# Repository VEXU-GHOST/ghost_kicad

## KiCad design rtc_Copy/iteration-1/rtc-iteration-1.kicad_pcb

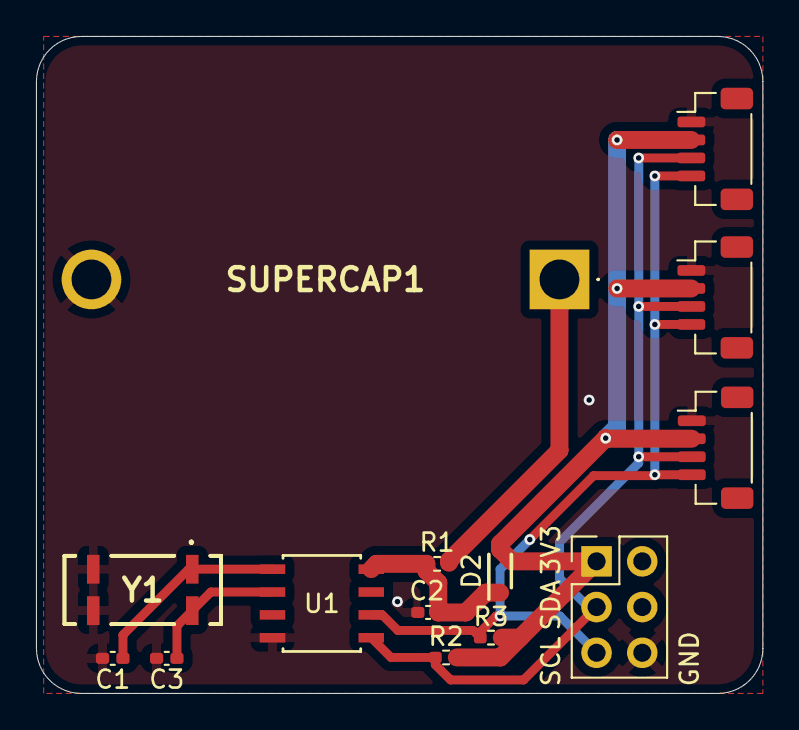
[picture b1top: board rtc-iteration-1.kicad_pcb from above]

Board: 2 copper layers, 40.4 x 36.5 mm, 14 parts (0 on the bottom side), 8 nets.

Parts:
C1, C3: 24p; C_0402_1005Metric_Pad0.74x0.62mm_HandSolder
C2: 0.1u; C_0402_1005Metric_Pad0.74x0.62mm_HandSolder
D2: RB751V-40X_R1; SODFL2512X90N
J1: Conn_02x03_Odd_Even; PinHeader_2x03_P2.54mm_Vertical
J2, J3, J4: Conn_01x04; JST_SH_BM04B-SRSS-TB_1x04-1MP_P1.00mm_Vertical
R1: 20k; R_0402_1005Metric_Pad0.72x0.64mm_HandSolder
R2, R3: 2.5k; R_0402_1005Metric_Pad0.72x0.64mm_HandSolder
SUPERCAP1: 5; CE5R5505HFZJ
U1: PCF8563T/5_518; PCF8563T_5_518_U_SO8_NXP
Y1: LFXTAL016178REEL

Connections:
+3.3V: D2.2 (A), J1.1, J2.2, J3.2, J4.2, R2.2, R3.2
GND: C1.2, C2.2, C3.2, J1.6, J2.1, J3.1, J4.1, SUPERCAP1.2 (-), U1.4 (VSS), Y1.2 (N/C_1), Y1.3 (N/C_2)
unnamed: C2.1, D2.1 (K), R1.2, U1.8 (VDD)
unnamed: R1.1, SUPERCAP1.1 (+)
unnamed: C1.1, U1.1 (OSCI), Y1.1 (CRYSTAL_1)
unnamed: C3.1, U1.2 (OSCO), Y1.4 (CRYSTAL_2)
scl: J1.5, J2.4, J3.4, J4.4, R3.1, U1.6 (SCL)
sda: J1.3, J2.3, J3.3, J4.3, R2.1, U1.5 (SDA)

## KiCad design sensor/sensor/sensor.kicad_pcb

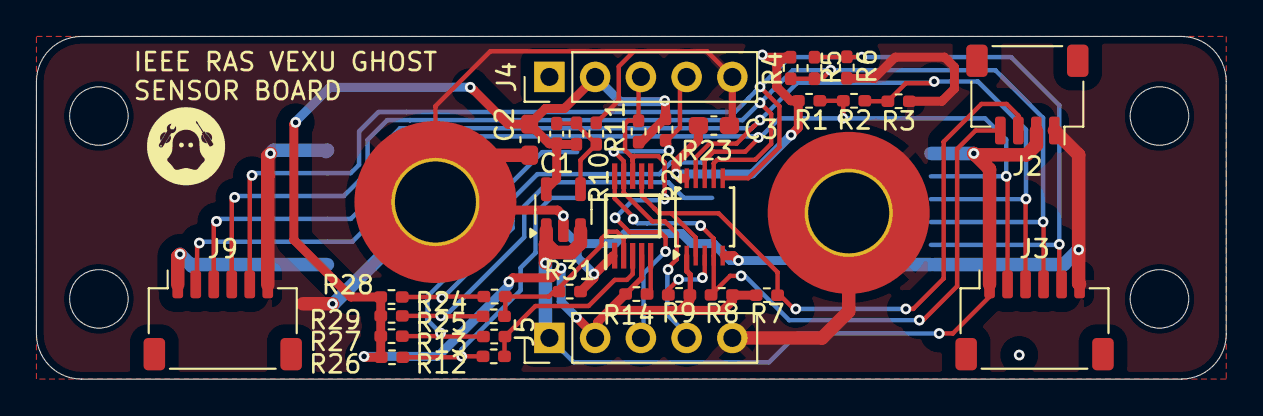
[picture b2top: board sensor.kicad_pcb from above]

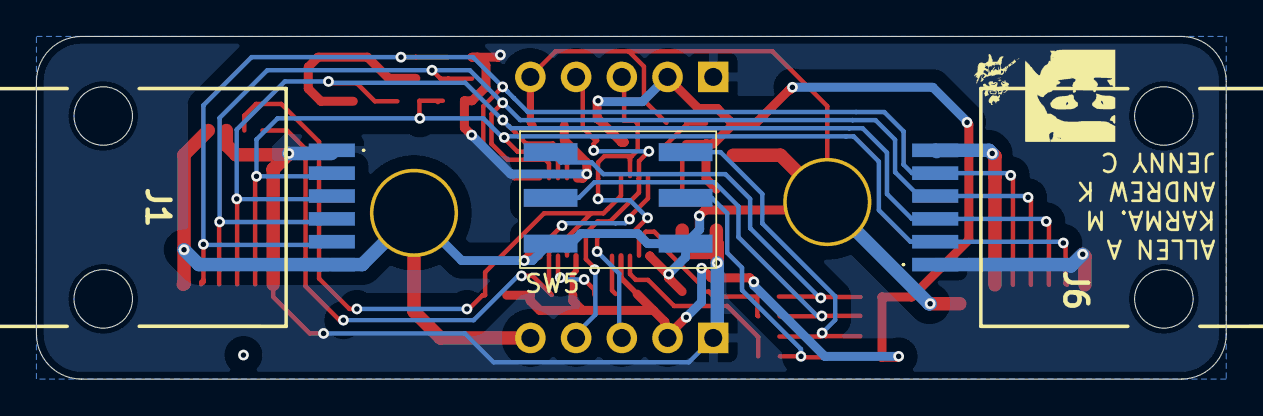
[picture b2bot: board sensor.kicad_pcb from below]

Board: 2 copper layers, 66.1 x 19.0 mm, 39 parts (3 on the bottom side), 20 nets.

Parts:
C1: 1n; C_0402_1005Metric_Pad0.74x0.62mm_HandSolder
C2, C3: 1u; C_0603_1608Metric_Pad1.08x0.95mm_HandSolder
H1, H2: MountingHole_Pad; MountingHole_4.5mm_Pad_TopOnly
IC1: LTC4316CMS#TRPBF; SOP50P490X110-10N
J1, J6: GDLX-SMT-N-66; GDLXSMTN66
J2: Conn_01x04; JST_SH_SM04B-SRSS-TB_1x04-1MP_P1.00mm_Horizontal
J3, J9: Conn_01x06; JST_SH_SM06B-SRSS-TB_1x06-1MP_P1.00mm_Horizontal
J4, J5: Conn_01x05; PinHeader_1x05_P2.54mm_Vertical
R1, R3, R4, R6: 600; R_0402_1005Metric_Pad0.72x0.64mm_HandSolder
R2, R5: 120; R_0402_1005Metric_Pad0.72x0.64mm_HandSolder
R7, R8, R22, R23: 4.7k; R_0402_1005Metric_Pad0.72x0.64mm_HandSolder
R9, R14, R26, R27: 10k; R_0402_1005Metric_Pad0.72x0.64mm_HandSolder
R10: 52k; R_0402_1005Metric_Pad0.72x0.64mm_HandSolder
R11: 30k; R_0402_1005Metric_Pad0.72x0.64mm_HandSolder
R12, R24: 400k; R_0402_1005Metric_Pad0.72x0.64mm_HandSolder
R13: 750k; R_0402_1005Metric_Pad0.72x0.64mm_HandSolder
R25: 780k; R_0402_1005Metric_Pad0.72x0.64mm_HandSolder
R28: 80k; R_0402_1005Metric_Pad0.72x0.64mm_HandSolder
R29: 40k; R_0402_1005Metric_Pad0.72x0.64mm_HandSolder
R31: 260k; R_0402_1005Metric_Pad0.72x0.64mm_HandSolder
SW5: SW_Coded_SH-7050; Rotary_Switch_16_pos
U1: PCA9615DP; TSSOP-10_3x3mm_P0.5mm
U5: TPS73101DBV; SOT-23-5

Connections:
+3.3V: C1.1, C2.1, IC1.4 (VCC), J4.2, J5.2, R7.1, R8.1, R9.1, R10.1, R14.2, R22.1, R23.1, R26.1, R27.1, R28.1, R29.1, U1.1 (V_{DD(A)}), U5.5 (OUT)
+5V: C3.1, J1.1, J2.2, J3.1, J4.1, J5.1, J6.1, J9.1, R1.1, R4.1, U1.10 (V_{DD(B)}), U5.1 (IN), U5.3 (EN)
/Sensors/scl: IC1.9 (SCLOUT), J4.4, J5.4, R23.2
/Sensors/sda: IC1.8 (SDAOUT), J4.3, J5.3, R22.2
GND: C2.2, C3.2, H1.1, H2.1, IC1.1 (GND), J1.6, J2.1, J3.6, J4.5, J5.5, J6.6, J9.6, R3.2, R6.2, R11.2, R31.2, SW5.C, U1.5 (V_{SS}), U5.2 (GND)
unnamed: IC1.5 (ENABLE), R14.1
unnamed: IC1.10 (SCLIN), J2.4, R8.2, U1.4 (SCL)
unnamed: IC1.7 (SDAIN), J2.3, R7.2, U1.2 (SDA)
unnamed: IC1.2 (XORH), R24.2, R25.2, R31.1
unnamed: IC1.3 (XORL), R12.2, R13.2
unnamed: J1.2, J3.2, J6.2, J9.2, R1.2, R2.2, U1.8 (DSDAP)
unnamed: J1.3, J3.3, J6.3, J9.3, R2.1, R3.1, U1.9 (DSDAM)
unnamed: J1.4, J3.4, J6.4, J9.4, R4.2, R5.2, U1.7 (DSCLP)
unnamed: J1.5, J3.5, J6.5, J9.5, R5.1, R6.1, U1.6 (DSCLM)
unnamed: R12.1, R26.2, SW5.1
unnamed: R13.1, R27.2, SW5.2
unnamed: R24.1, R28.2, SW5.4
unnamed: R25.1, R29.2, SW5.8
unnamed: R9.2, U1.3 (EN)
unnamed: C1.2, R10.2, R11.1, U5.4 (FB)

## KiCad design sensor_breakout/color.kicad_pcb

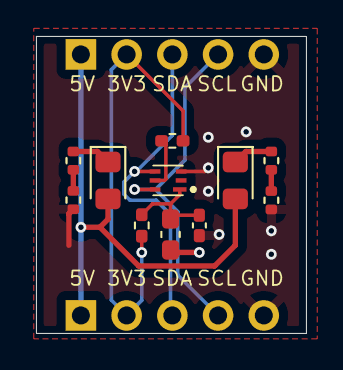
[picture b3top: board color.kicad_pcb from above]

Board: 2 copper layers, 15.0 x 16.5 mm, 13 parts (0 on the bottom side), 11 nets.

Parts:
C4: 1u; C_0603_1608Metric_Pad1.08x0.95mm_HandSolder
C5: 0.1u; C_0402_1005Metric_Pad0.74x0.62mm_HandSolder
D1, D2: WHITE; LED_0805_2012Metric_Pad1.15x1.40mm_HandSolder
IC2: ISL29125IROZ-T7; ISL29125IROZT7
J4, J4#2: Conn_01x05; PinHeader_1x05_P2.54mm_Vertical
R15: 100; R_0402_1005Metric_Pad0.72x0.64mm_HandSolder
R16: 4.7k; R_0402_1005Metric_Pad0.72x0.64mm_HandSolder
R17, R18, R30, R32: 120; R_0402_1005Metric

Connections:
+3.3V: J4.2, J4#2.2, R15.2, R16.1
+5V: D1.2 (A), D2.2 (A), J4.1, J4#2.1
/scl: IC2.6 (SCL), J4.4, J4#2.4
/sda: IC2.4 (SDA), J4.3, J4#2.3
GND: C4.2, C5.2, IC2.3 (GND), J4.5, J4#2.5, R30.2, R32.2
unnamed: D1.1 (K), R17.1
unnamed: D2.1 (K), R18.1
unnamed: C4.1, C5.1, IC2.1 (VDD), R15.1
unnamed: IC2.5 (~INT), R16.2
unnamed: R17.2, R30.1
unnamed: R18.2, R32.1

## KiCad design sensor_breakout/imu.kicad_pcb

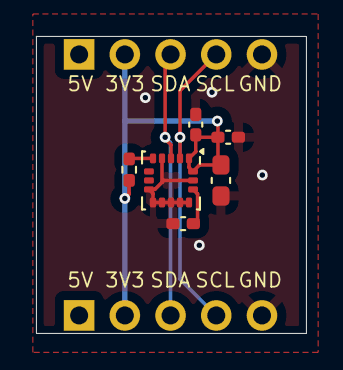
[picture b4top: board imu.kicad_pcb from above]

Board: 2 copper layers, 15.0 x 16.5 mm, 8 parts (0 on the bottom side), 7 nets.

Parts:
C7, C10: 0.1u; C_0402_1005Metric_Pad0.74x0.62mm_HandSolder
C8: 2.2u; C_0603_1608Metric_Pad1.08x0.95mm_HandSolder
C9: 10n; C_0402_1005Metric_Pad0.74x0.62mm_HandSolder
J4, J4#2: Conn_01x05; PinHeader_1x05_P2.54mm_Vertical
R19: 4.7k; R_0402_1005Metric_Pad0.72x0.64mm_HandSolder
U6: ICM-20602; LGA-16_3x3mm_P0.5mm_LayoutBorder3x5y

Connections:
+3.3V: C7.1, C8.1, C9.1, J4.2, J4#2.2, R19.1, U6.1 (VDDIO), U6.16 (VDD)
+5V: J4.1, J4#2.1
/scl: J4.4, J4#2.4, U6.2 (SCL/SPC)
/sda: J4.3, J4#2.3, U6.3 (SDA/SDI)
GND: C7.2, C8.2, C9.2, C10.2, J4.5, J4#2.5, U6.4 (SAO/SD0), U6.8 (FSYNC), U6.9 (GND), U6.10 (GND), U6.11 (GND), U6.12 (GND), U6.13 (GND), U6.15 (GND)
unnamed: C10.1, U6.14 (REGOUT)
unnamed: R19.2, U6.5 (~CS)

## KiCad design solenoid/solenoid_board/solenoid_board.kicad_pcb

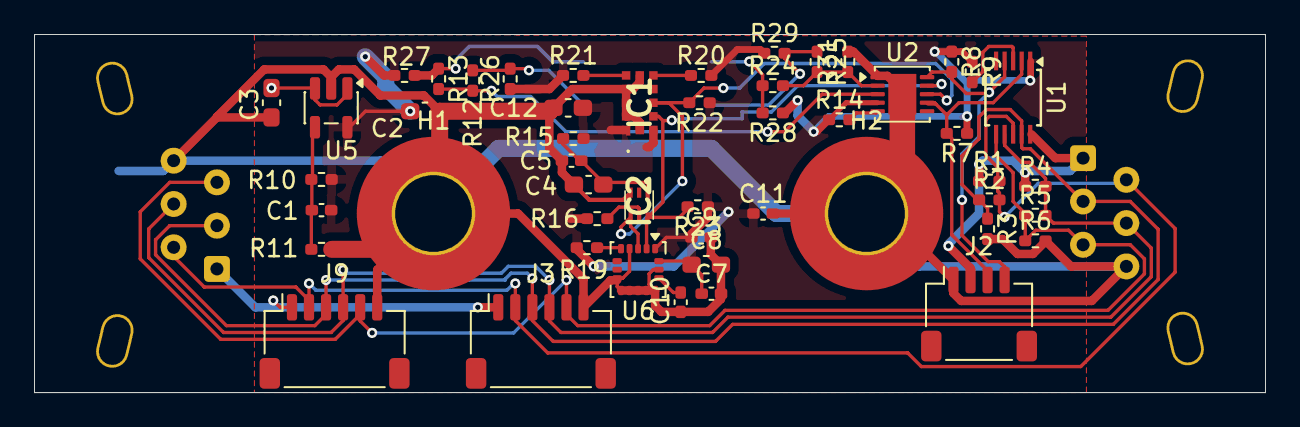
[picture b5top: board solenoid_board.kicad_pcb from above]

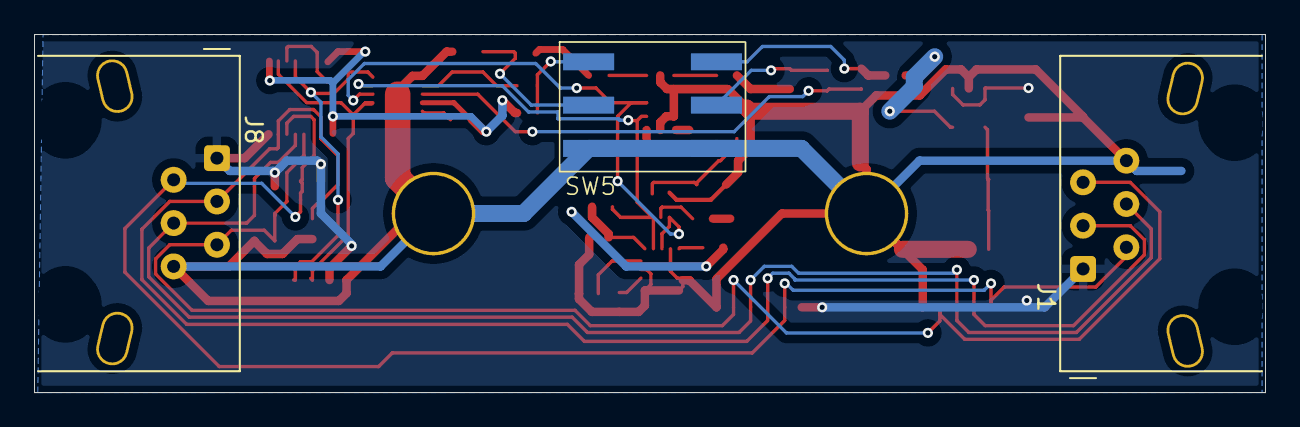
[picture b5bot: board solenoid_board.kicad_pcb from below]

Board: 4 copper layers, 72.2 x 21.0 mm, 53 parts (3 on the bottom side), 26 nets.

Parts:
C1: 1n; C_0402_1005Metric_Pad0.74x0.62mm_HandSolder
C2, C3, C4: 1u; C_0603_1608Metric_Pad1.08x0.95mm_HandSolder
C5, C7, C10, C11: 0.1u; C_0402_1005Metric_Pad0.74x0.62mm_HandSolder
C8: 2.2u; C_0603_1608Metric_Pad1.08x0.95mm_HandSolder
C9: 10n; C_0402_1005Metric_Pad0.74x0.62mm_HandSolder
C12: 4.7u; C_0603_1608Metric_Pad1.08x0.95mm_HandSolder
H1, H2: MountingHole_Pad; MountingHole_4.5mm_Pad_TopOnly
IC1: VL53L4CDV0DH_1; VL53L4CDV0DH1
IC2: ISL29125IROZ-T7; ISL29125IROZT7
J1, J8: RJ12_Shielded; RJ12_Pin_Connector
J2: Conn_01x04; JST_SH_SM04B-SRSS-TB_1x04-1MP_P1.00mm_Horizontal
J3, J9: Conn_01x06; JST_SH_SM06B-SRSS-TB_1x06-1MP_P1.00mm_Horizontal
R1, R3, R4, R6: 600; R_0402_1005Metric_Pad0.72x0.64mm_HandSolder
R2, R5: 120; R_0402_1005Metric_Pad0.72x0.64mm_HandSolder
R7, R8, R16, R19, R22, R23: 4.7k; R_0402_1005Metric_Pad0.72x0.64mm_HandSolder
R9, R14, R20, R21, R26, R27: 10k; R_0402_1005Metric_Pad0.72x0.64mm_HandSolder
R10: 52k; R_0402_1005Metric_Pad0.72x0.64mm_HandSolder
R11: 30k; R_0402_1005Metric_Pad0.72x0.64mm_HandSolder
R12, R24: 400k; R_0402_1005Metric_Pad0.72x0.64mm_HandSolder
R13: 750k; R_0402_1005Metric_Pad0.72x0.64mm_HandSolder
R15: 100; R_0402_1005Metric_Pad0.72x0.64mm_HandSolder
R25: 780k; R_0402_1005Metric_Pad0.72x0.64mm_HandSolder
R28: 80k; R_0402_1005Metric_Pad0.72x0.64mm_HandSolder
R29: 40k; R_0402_1005Metric_Pad0.72x0.64mm_HandSolder
R31: 260k; R_0402_1005Metric_Pad0.72x0.64mm_HandSolder
SW5: SW_Coded_SH-7050; Rotary_Switch_16_pos
U1: PCA9615DP; TSSOP-10_3x3mm_P0.5mm
U2: LTC4316xDD; DFN-10-1EP_3x3mm_P0.5mm_EP1.65x2.38mm
U5: TPS73101DBV; SOT-23-5
U6: ICM-20602; LGA-16_3x3mm_P0.5mm_LayoutBorder3x5y

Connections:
+3.3V: C1.1, C2.1, C7.1, C8.1, C9.1, C11.1, C12.1, IC1.1 (AVDDVCSEL_1), IC1.11 (AVDD), IC1.13 (AVDDVCSEL_2), R7.1, R8.1, R9.1, R10.1, R14.1, R15.2, R16.1, R19.1, R20.2, R21.1, R22.1, R23.1, R26.1, R27.1, R28.1, R29.1, U1.1 (V_{DD(A)}), U2.4 (V_{CC}), U5.5 (OUT), U6.1 (VDDIO), U6.16 (VDD)
+5V: C3.1, J1.1, J2.2, J3.1, J8.1, J9.1, R1.1, R4.1, U1.10 (V_{DD(B)}), U5.1 (IN), U5.3 (EN)
/Sensors/scl: IC1.10 (SCL), IC2.6 (SCL), R23.2, U2.9 (SCLOUT), U6.2 (SCL/SPC)
/Sensors/sda: IC1.9 (SDA), IC2.4 (SDA), R22.2, U2.8 (SDAOUT), U6.3 (SDA/SDI)
GND: C2.2, C3.2, C4.2, C5.2, C7.2, C8.2, C9.2, C10.2, C11.2, C12.2, H1.1, H2.1, IC1.2 (AVSSVCSEL), IC1.3 (GND), IC1.4 (GND2), IC1.6 (GND3), IC1.12 (GND4), IC2.3 (GND), J1.6, J2.1, J3.6, J8.6, J9.6, R3.2, R6.2, R11.2, R31.2, SW5.C, U1.5 (V_{SS}), U2.1 (GND), U2.11 (EP), U5.2 (GND), U6.4 (SAO/SD0), U6.8 (FSYNC), U6.9 (GND), U6.10 (GND), U6.11 (GND), U6.12 (GND), U6.13 (GND), U6.15 (GND)
unnamed: IC1.7 (GPIO1), R20.1
unnamed: IC1.5 (XSHUT), R21.2
unnamed: C4.1, C5.1, IC2.1 (VDD), R15.1
unnamed: IC2.5 (~INT), R16.2
unnamed: J2.3, R7.2, U1.2 (SDA), U2.7 (SDAIN)
unnamed: J2.4, R8.2, U1.4 (SCL), U2.10 (SCLIN)
unnamed: J1.2, J3.2, J8.2, J9.2, R1.2, R2.2, U1.8 (DSDAP)
unnamed: J1.3, J3.3, J8.3, J9.3, R2.1, R3.1, U1.9 (DSDAM)
unnamed: J1.4, J3.4, J8.4, J9.4, R4.2, R5.2, U1.7 (DSCLP)
unnamed: J1.5, J3.5, J8.5, J9.5, R5.1, R6.1, U1.6 (DSCLM)
unnamed: R12.1, R26.2, SW5.1
unnamed: R13.1, R27.2, SW5.2
unnamed: R24.1, R28.2, SW5.4
unnamed: R25.1, R29.2, SW5.8
unnamed: R9.2, U1.3 (EN)
unnamed: R14.2, U2.5 (ENABLE)
unnamed: R24.2, R25.2, R31.1, U2.2 (XORH)
unnamed: R12.2, R13.2, U2.3 (XORL)
unnamed: C1.2, R10.2, R11.1, U5.4 (FB)
unnamed: C10.1, U6.14 (REGOUT)
unnamed: R19.2, U6.5 (~CS)

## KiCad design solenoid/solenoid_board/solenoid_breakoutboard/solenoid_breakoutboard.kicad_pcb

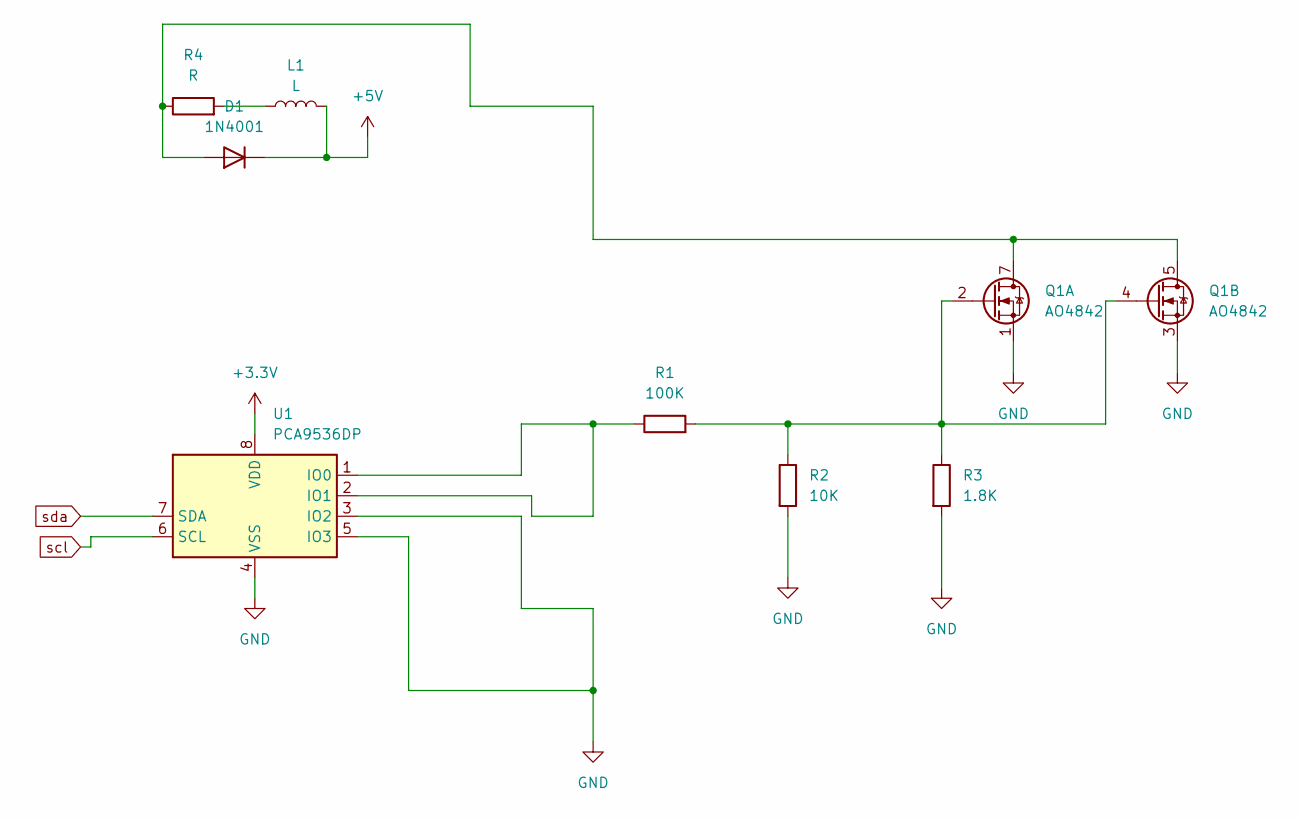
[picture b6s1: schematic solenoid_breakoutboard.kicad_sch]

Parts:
D1: 1N4001; D_DO-41_SOD81_P10.16mm_Horizontal
L1: L; L_Radial_D10.0mm_P5.00mm_Fastron_07M
Q1: AO4842; SOIC-8_3.9x4.9mm_P1.27mm
R1: 100K; R_0805_2012Metric
R2: 10K; R_0805_2012Metric
R3: 1.8K; R_0805_2012Metric
R4: R; R_0805_2012Metric
U1: PCA9536DP; TSSOP-8_3x3mm_P0.65mm

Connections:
+3.3V: U1.8 (VDD)
+5V: D1.1 (K), L1.2
GND: Q1.1 (S1), Q1.3 (S2), R2.2, R3.2, U1.3 (IO2), U1.4 (VSS), U1.5 (IO3)
unnamed: D1.2 (A), Q1.5 (D2), Q1.6 (D2), Q1.7 (D1), Q1.8 (D1), R4.1
unnamed: L1.1, R4.2
unnamed: Q1.2 (G1), Q1.4 (G2), R1.2, R2.1, R3.1
unnamed: R1.1, U1.1 (IO0), U1.2 (IO1)
scl: U1.6 (SCL)
sda: U1.7 (SDA)

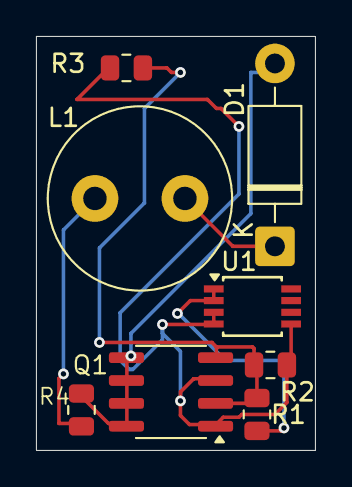
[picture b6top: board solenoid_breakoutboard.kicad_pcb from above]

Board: 2 copper layers, 15.5 x 23.0 mm, 8 parts (0 on the bottom side), 6 nets.

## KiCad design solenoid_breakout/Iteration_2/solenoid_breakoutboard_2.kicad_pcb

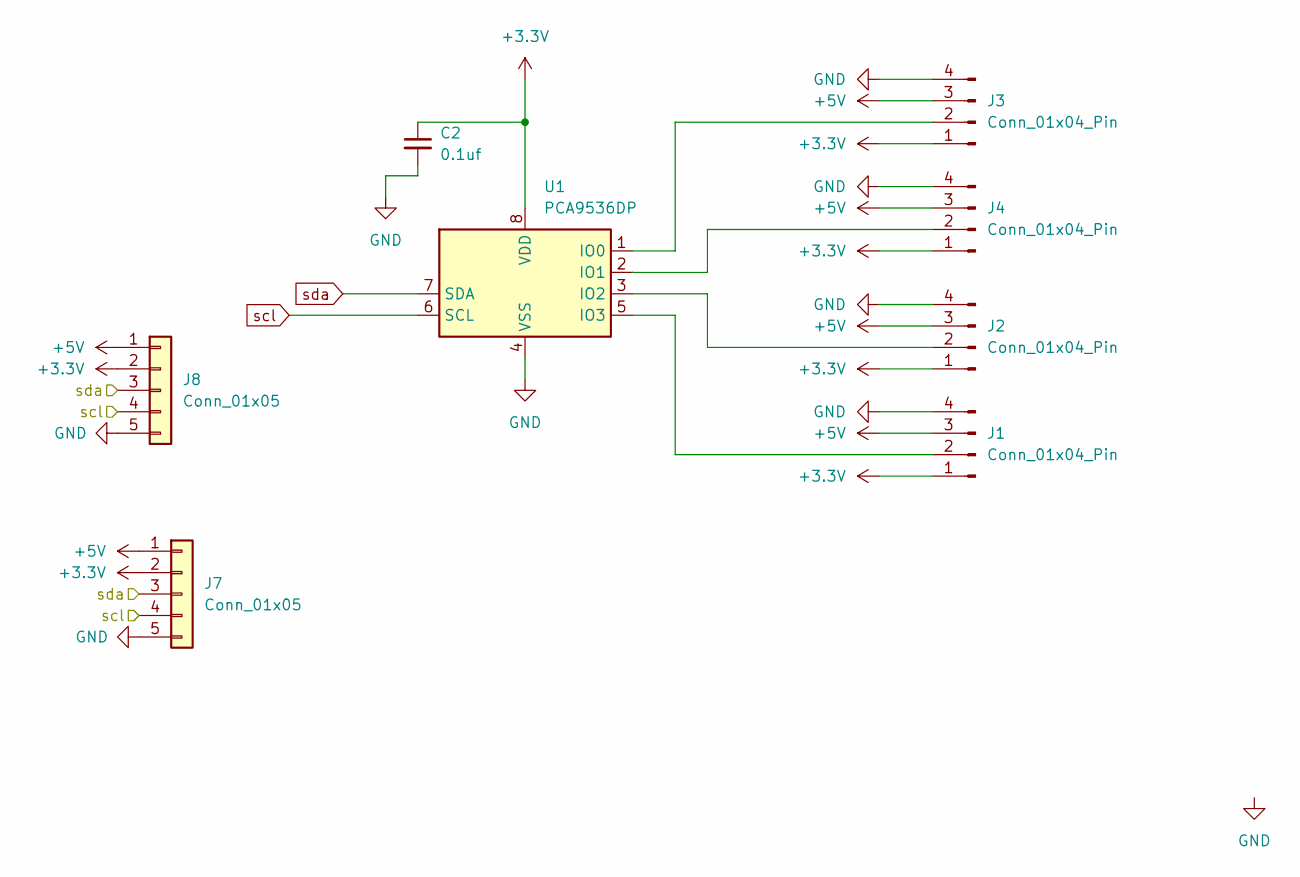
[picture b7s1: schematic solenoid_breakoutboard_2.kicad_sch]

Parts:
C2: 0.1uf; C_0603_1608Metric
J1, J2, J3, J4: Conn_01x04_Pin; PinHeader_1x04_P2.54mm_Vertical
J7, J8: Conn_01x05; PinHeader_1x05_P2.54mm_Vertical
U1: PCA9536DP; TSSOP-8_3x3mm_P0.65mm

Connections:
+3.3V: C2.1, J1.1, J2.1, J3.1, J4.1, J7.2, J8.2, U1.8 (VDD)
+5V: J1.3, J2.3, J3.3, J4.3, J7.1, J8.1
GND: C2.2, J1.4, J2.4, J3.4, J4.4, J7.5, J8.5, U1.4 (VSS)
unnamed: J1.2, U1.5 (IO3)
unnamed: J2.2, U1.3 (IO2)
unnamed: J3.2, U1.1 (IO0)
unnamed: J4.2, U1.2 (IO1)
scl: J7.4, J8.4, U1.6 (SCL)
sda: J7.3, J8.3, U1.7 (SDA)

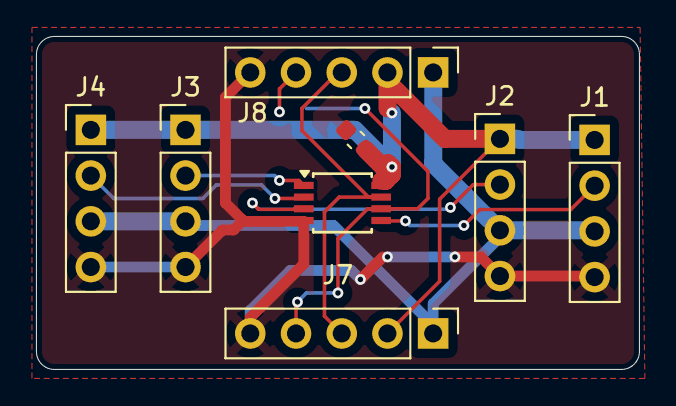
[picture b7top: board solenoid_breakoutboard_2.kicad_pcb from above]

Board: 2 copper layers, 33.5 x 18.5 mm, 8 parts (0 on the bottom side), 9 nets.
